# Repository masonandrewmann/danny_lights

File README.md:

# the cyberbar - wifi artnet/dmx + IR led lighting fixtures 
using ESP8266 for individually addressable LED bars controllable through both IR remote and wifi Artnet network

## User Guide!
Hello and welcome to the *magical* light fixtures that can be controlled via a handy 44 key infrared remote OR from a lighting console, computer, or mobile device via DMX lighting protocol. This is a walkthrough of how to use the lights. 

### IR remote mode

Put switch in IR position and use your 44 key remote! Here is what it does:

### Wifi Artnet/DMX mode
#### WIFI setup 
  - put switch in DMX position
  - It will initially be in "Access Point" mode. Connect to the device as you would connect to a new wifi router. It will be called 'Cyberbar' initially in your wifi setup. 
    - username: CyberBar1 (or 2 or 3)
    - password: password
  - Once you are connected to it, you should be taken to IP address **192.168.4.1** in your browswer. The screen should look like this: 

  - ArtNet typically starts at Universe 0! Check your console/lighting program for what universe you start at. 
  - Set the DMX address. 
  - If you want to connect multiple fixtures together, or use this in conjunction with something else, click the link to change the wifi settings. The page will look like this:
  
  - you can change the name of the fixture, and connect to another wifi network using its SSID and Password. This way you can connect many fixutres on the same network, or connect the fixture to the internet to control remotely.  
  - **reset button:** hold while turning on to reset the WIFI network to access point mode. 

#### DMX settings
  - set as 3 channel fixtures with 32 pixels in each fixture ([example setup shown here](https://htmlpreview.github.io/?https://github.com/masonandrewmann/danny_lights/blob/master/lightjams_starter/patch.html))
    - color mode = RGB

behold the beauty!

## installation guide for setting up your own:
I am assuming you are using the classic Arduino IDE!
 
IR code was modifed from [dmonty2's wonderful repo](https://github.com/dmonty2/ir_remote_leds)

make sure you install ESP8266 board add-ons for the IDE, [here](https://randomnerdtutorials.com/how-to-install-esp8266-board-arduino-ide/) is instructions on how to do that 

Only tested with ESP8266 using "NodMCU 1.0 (ESP-12E Module)" as the board. 

### required libraries: 
IOT and WIFI stuff: 
 - [IOTWebConf.h](https://github.com/prampec/IotWebConf) // NOTE: This library has been modified so that it stores in EEPROM starting at address 8 instead of 0, use the version included in this repository rather than the official release OR change the line "# define IOTWEBCONF_CONFIG_START 0" to "# define IOTWEBCONF_CONFIG_START 8" in IotWebConf.h in the official release. **The updated file is in library/IotWebConf.h. Move this into your Arduino library folder!**
- [ArtnetWifi.h ](https://github.com/natcl/Artnet) - not to be confused with other artnet wifi libraries,  this is the one to use

LED stuff: 
- [Adafruit_NeoPixel.h](https://github.com/adafruit/Adafruit_NeoPixel)
- [FastLED](https://github.com/FastLED/FastLED)
  
Infrared (IR) reciever stuff: 
- [IRRemoteESP8266](https://github.com/crankyoldgit/IRremoteESP8266)
-  [IRremote](https://github.com/NicoHood/IRLremote)  (outdated?)

Misc Libraries to include: 
- EEPROM.h , should be inheirited from the ESP8266 board library 

### hardware notes
Here are the interals: 

Here is the schematic: 

Included in the repo is a KiCad file for a PCB for the ESP8266:

## pinout for esp8266

LEDPIN          16 // D0    (built in indicator)

BUTTONPIN       13 // D7    (reset button)

MODEPIN         12 // D6    (dmx or IR)

ir recieiver =  14 // D5

led output     2 // D4      (addressable led output)

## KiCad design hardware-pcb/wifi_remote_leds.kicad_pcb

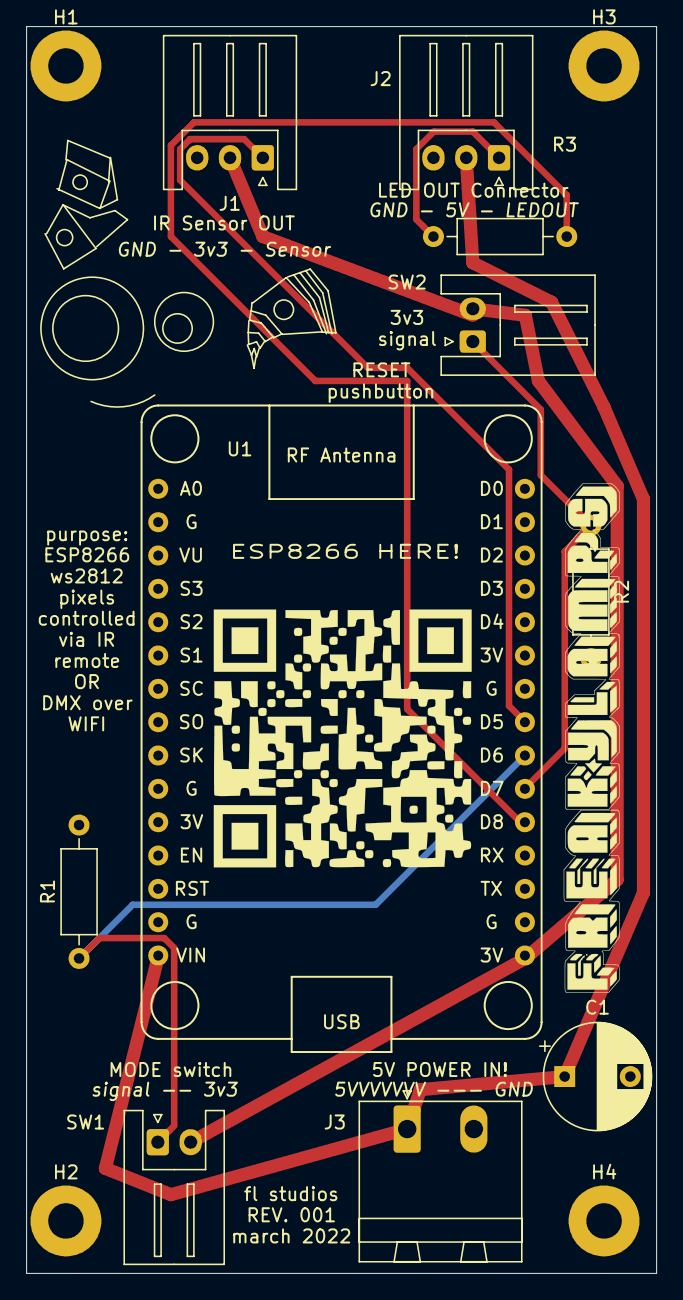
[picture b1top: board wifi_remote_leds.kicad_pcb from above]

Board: 2 copper layers, 48.0 x 95.0 mm, 14 parts (0 on the bottom side), 8 nets.

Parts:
C1: 1000uF; CP_Radial_D8.0mm_P5.00mm
H1, H2, H3, H4: MountingHole; MountingHole_2.7mm_M2.5_Pad
J1: IR_connector; JST_XH_S3B-XH-A_1x03_P2.50mm_Horizontal
J2: LED out connector; JST_XH_S3B-XH-A_1x03_P2.50mm_Horizontal
J3: POWER IN; PhoenixContact_MSTBA_2,5_2-G-5,08_1x02_P5.08mm_Horizontal
R1, R2: 10k; R_Axial_DIN0207_L6.3mm_D2.5mm_P10.16mm_Horizontal
R3: 470; R_Axial_DIN0207_L6.3mm_D2.5mm_P10.16mm_Horizontal
SW1: SW_SPST; JST_XH_S2B-XH-A_1x02_P2.50mm_Horizontal
SW2: SW_Push; JST_XH_S2B-XH-A_1x02_P2.50mm_Horizontal
U1: NodeMCU_1.0_(ESP-12E); NodeMCU1.0(12-E)

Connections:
3v3: J1.2, SW1.2, SW2.2, U1.16
+5V: C1.1, J2.2, J3.1, U1.15
GND: C1.2, J1.3, J2.3, J3.2, R1.2, R2.2, U1.10, U1.14, U1.17, U1.24
IR_SENSOR: J1.1, U1.23
LED_OUT: J2.1, R3.1
MODE_SW: R1.1, SW1.1, U1.22
unnamed: R3.2, U1.20
RESET_PB: R2.1, SW2.1, U1.21

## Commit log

2020-12-11 testing...
2020-12-12 webserver inputs for DMX address and universe
2020-12-12 dmx configuration stored in EEPROM
2021-01-07 added mode switch button on GPIO15 (D8 on dev board). Wired with a 10k pulldown
2021-01-07 button pin switched to GPIO13 (D7). Integrated access point and DMX input code.
2021-01-07 fixed EEPROM overwriting issue and cleaned some print statements
2021-01-07 cleanup
2021-01-07 file cleanup
2021-01-07 removed commented out code
2021-01-07 Add files via upload
    artnet over wifi sketch from Fly On A Wall frames. Included is a watchdog function that puts the thing to sleep if its not connected to a network. we can take that out. we should make it so that it h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
2021-01-09 created new branch
2021-01-09 fixed filestructue
2021-01-09 wifi control works
2021-01-10 artnet control code integrated
2021-01-10 removed extraneous files
2021-01-10 removed unused libraries
2021-01-10 removed more unused libraries
2021-01-10 removed even more unused libraries :0
2021-02-03 began integrating IR remote control
2021-02-09 IR code adapted to ESP8266
2021-02-09 began integrating artnet and ir, fixed EEPROM overlap
2021-02-09 fixed EEPROM for real and integrated the two program modes
2021-02-10 some minor changes, commiting for consistency
2021-03-02 fixed gradient mode
2021-03-02 eeprom recalls previous settings
2021-03-03 diy color picker added
2021-03-03 fixed a bug where bad IR values would exit diy mode
2021-03-03 eeprom fixed with commit messages
2022-05-23 code-ap names, new pinouts etc
2022-05-26 cleaning up
2022-05-26 readme
2022-05-26 readme and more
2022-05-26 finalizing changes in readme, cyberbar1 is default code now
2022-05-26 small readme changes
